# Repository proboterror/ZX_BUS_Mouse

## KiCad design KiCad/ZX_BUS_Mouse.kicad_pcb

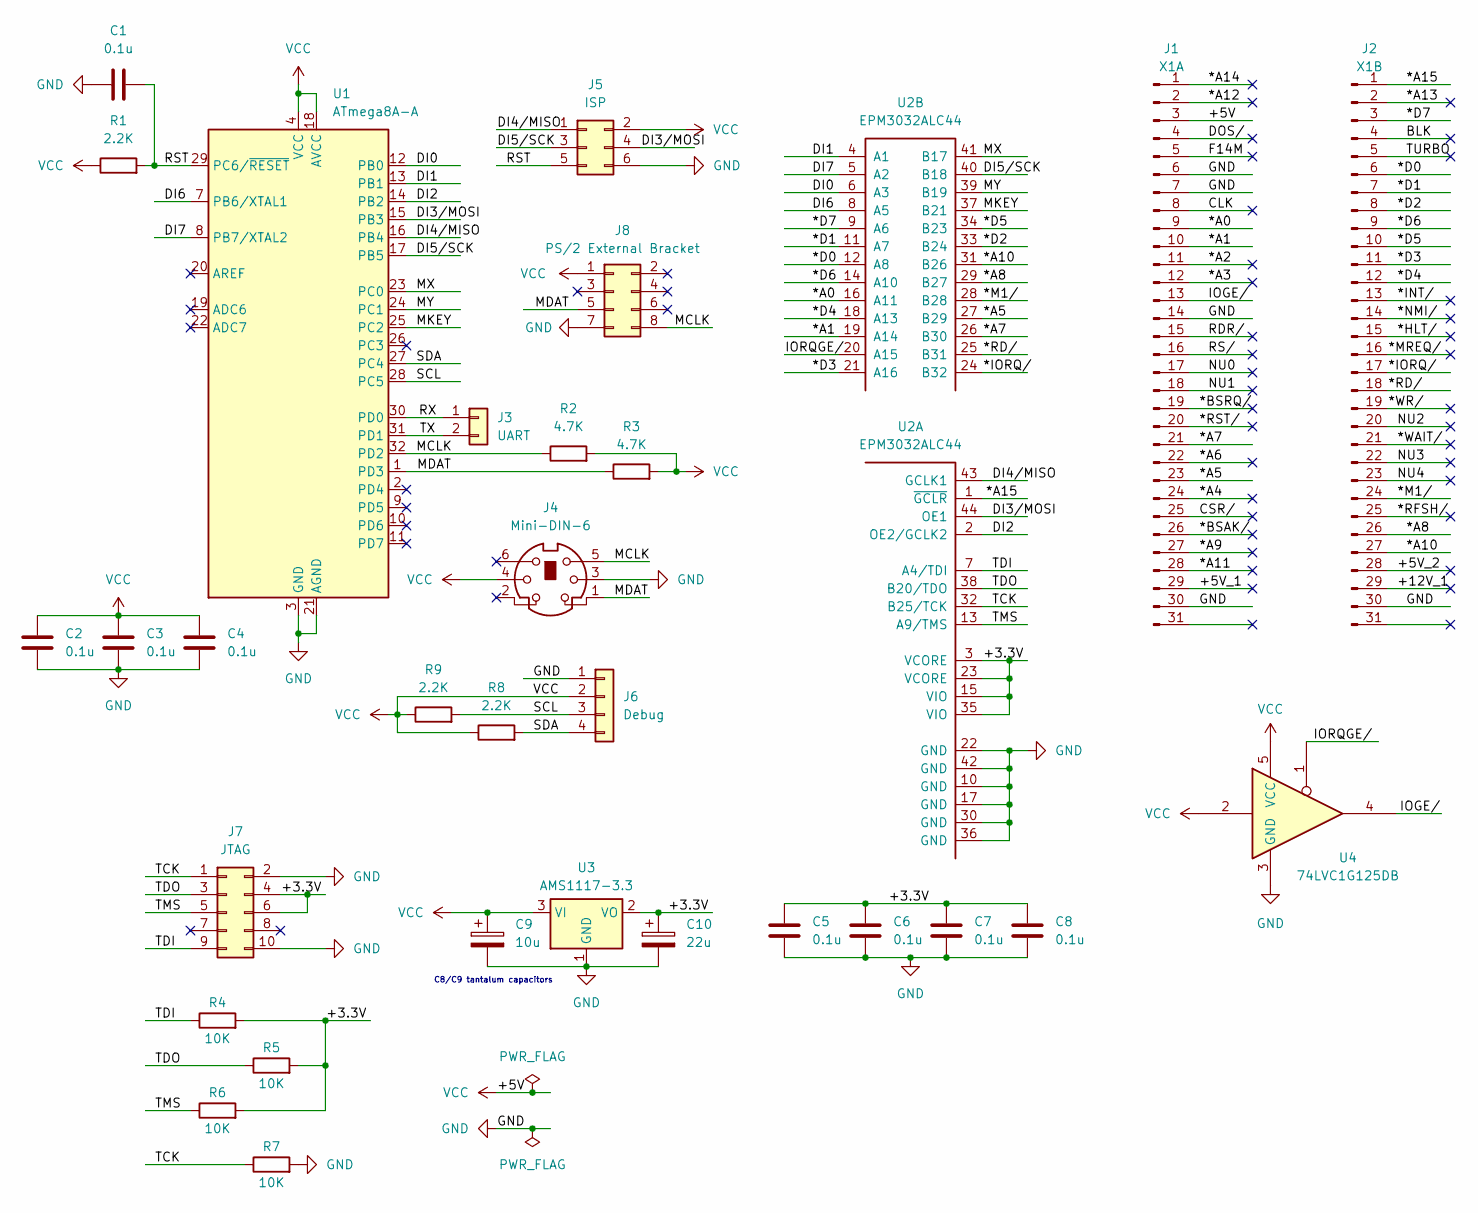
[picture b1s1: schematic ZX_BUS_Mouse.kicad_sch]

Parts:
C1, C2, C3, C4, C5, C6, C7, C8: 0.1u; C_1206_3216Metric_Pad1.33x1.80mm_HandSolder
C9: 10u; CP_EIA-6032-28_Kemet-C_Pad2.25x2.35mm_HandSolder
C10: 22u; CP_EIA-6032-28_Kemet-C_Pad2.25x2.35mm_HandSolder
J1: X1A; PinSocket_1x31_P2.54mm_2
J2: X1B; PinSocket_1x31_P2.54mm_2
J3: UART; PinHeader_1x02_P2.54mm_Vertical
J4: Mini-DIN-6; Connector_Mini-DIN_Female_6Pin_2rows
J5: ISP; PinHeader_2x03_P2.54mm_Vertical
J6: Debug; PinHeader_1x04_P2.54mm_Vertical
J7: JTAG; IDC-Header_2x05_P2.54mm_Vertical
J8: PS/2 External Bracket; PinHeader_2x04_P2.54mm_Vertical
R1, R8, R9: 2.2K; R_1206_3216Metric_Pad1.30x1.75mm_HandSolder
R2, R3: 4.7K; R_1206_3216Metric_Pad1.30x1.75mm_HandSolder
R4, R5, R6, R7: 10K; R_1206_3216Metric_Pad1.30x1.75mm_HandSolder
U1: ATmega8A-A; TQFP-32_7x7mm_P0.8mm
U2: EPM3032ALC44; PLCC-44_THT-Socket; MPN EPM3032ALC44-{grade}
U3: AMS1117-3.3; SOT-223-3_TabPin2
U4: 74LVC1G125DB; SOT-23-5_HandSoldering

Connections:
/*A0: J1.9, U2.16 (A11)
/*A1: J1.10, U2.19 (A14)
/*A2: J1.11
/*A3: J1.12
/*A4: J1.24
/*A5: J1.23, U2.27 (B29)
/*A6: J1.22
/*A7: J1.21, U2.26 (B30)
/*A8: J2.26, U2.29 (B27)
/*A9: J1.27
/*A10: J2.27, U2.31 (B26)
/*A11: J1.28
/*A12: J1.2
/*A13: J2.2
/*A14: J1.1
/*A15: J2.1, U2.1 (~GCLR)
/*BSAK/: J1.26
/*BSRQ/: J1.19
/*D0: J2.6, U2.12 (A8)
/*D1: J2.7, U2.11 (A7)
/*D2: J2.8, U2.33 (B24)
/*D3: J2.11, U2.21 (A16)
/*D4: J2.12, U2.18 (A13)
/*D5: J2.10, U2.34 (B23)
/*D6: J2.9, U2.14 (A10)
/*D7: J2.3, U2.9 (A6)
/*HLT/: J2.15
/*INT/: J2.13
/*IORQ/: J2.17, U2.24 (B32)
/*M1/: J2.24, U2.28 (B28)
/*MREQ/: J2.16
/*NMI/: J2.14
/*RD/: J2.18, U2.25 (B31)
/*RFSH/: J2.25
/*RST/: J1.20
/*WAIT/: J2.21
/*WR/: J2.19
/+3.3V: C5.1, C6.1, C7.1, C8.1, C10.1, J7.4, J7.6, R4.2, R5.2, R6.2, U2.3 (VCORE), U2.15 (VIO), U2.23 (VCORE), U2.35 (VIO), U3.2 (VO)
/+5V_1: J1.29
/+5V_2: J2.28
/+12V_1: J2.29
/BLK: J2.4
/CLK: J1.8
/CSR/: J1.25
/DI0: U1.12 (PB0), U2.6 (A3)
/DI1: U1.13 (PB1), U2.4 (A1)
/DI2: U1.14 (PB2), U2.2 (OE2/GCLK2)
/DI3/MOSI: J5.4, U1.15 (PB3), U2.44 (OE1)
/DI4/MISO: J5.1, U1.16 (PB4), U2.43 (GCLK1)
/DI5/SCK: J5.3, U1.17 (PB5), U2.40 (B18)
/DI6: U1.7 (PB6/XTAL1), U2.8 (A5)
/DI7: U1.8 (PB7/XTAL2), U2.5 (A2)
/DOS/: J1.4
/F14M: J1.5
/IOGE/: J1.13, U4.4
/IORQGE/: U2.20 (A15), U4.1
/MCLK: J4.5, J8.8, R2.1, U1.32 (PD2)
/MDAT: J4.1, J8.5, R3.1, U1.1 (PD3)
/MKEY: U1.25 (PC2), U2.37 (B21)
/MX: U1.23 (PC0), U2.41 (B17)
/MY: U1.24 (PC1), U2.39 (B19)
/NU0: J1.17
/NU1: J1.18
/NU2: J2.20
/NU3: J2.22
/NU4: J2.23
/RDR/: J1.15
/RST: C1.2, J5.5, R1.2, U1.29 (PC6/~RESET)
/RS/: J1.16
/RX: J3.1, U1.30 (PD0)
/SCL: J6.3, R9.2, U1.28 (PC5)
/SDA: J6.4, R8.2, U1.27 (PC4)
/TCK: J7.1, R7.1, U2.32 (B25/TCK)
/TDI: J7.9, R4.1, U2.7 (A4/TDI)
/TDO: J7.3, R5.1, U2.38 (B20/TDO)
/TMS: J7.5, R6.1, U2.13 (A9/TMS)
/TURBO: J2.5
/TX: J3.2, U1.31 (PD1)
GND: C1.1, C2.2, C3.2, C4.2, C5.2, C6.2, C7.2, C8.2, C9.2, C10.2, J1.6, J1.7, J1.14, J1.30, J2.30, J4.3, J5.6, J6.1, J7.2, J7.10, J8.7, R7.2, U1.3 (GND), U1.5 (GND), U1.21 (AGND), U2.10 (GND), U2.17 (GND), U2.22 (GND), U2.30 (GND), U2.36 (GND), U2.42 (GND), U3.1 (GND), U4.3 (GND)
VCC: C2.1, C3.1, C4.1, C9.1, J1.3, J4.4, J5.2, J6.2, J8.1, R1.1, R2.2, R3.2, R8.1, R9.1, U1.4 (VCC), U1.6 (VCC), U1.18 (AVCC), U3.3 (VI), U4.2, U4.5 (VCC)

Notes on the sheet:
C8/C9 tantalum capacitors

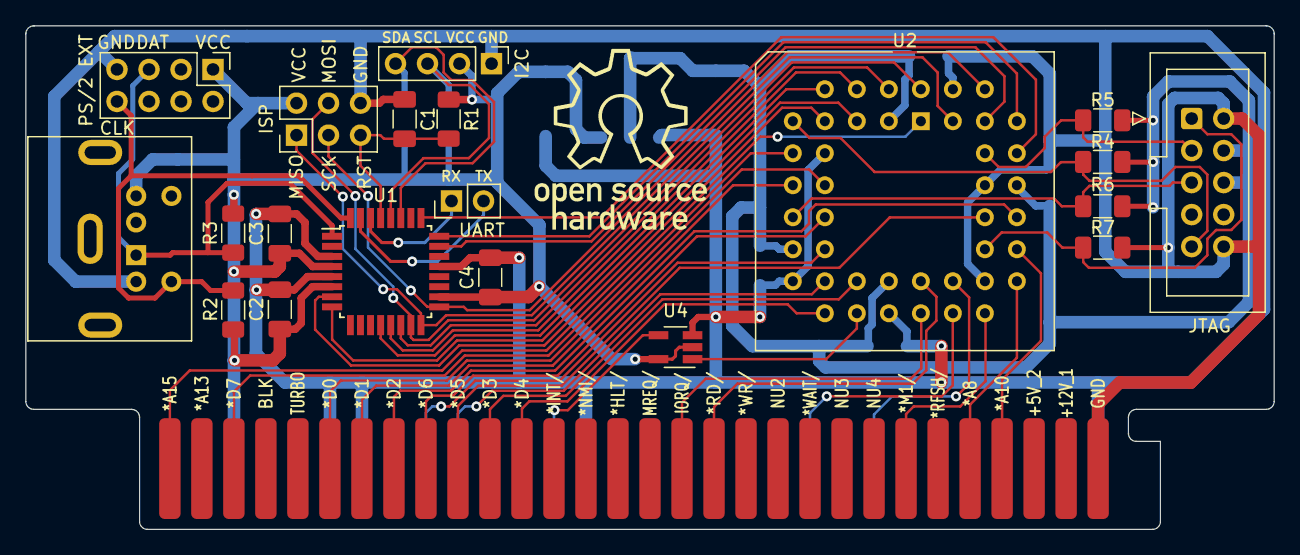
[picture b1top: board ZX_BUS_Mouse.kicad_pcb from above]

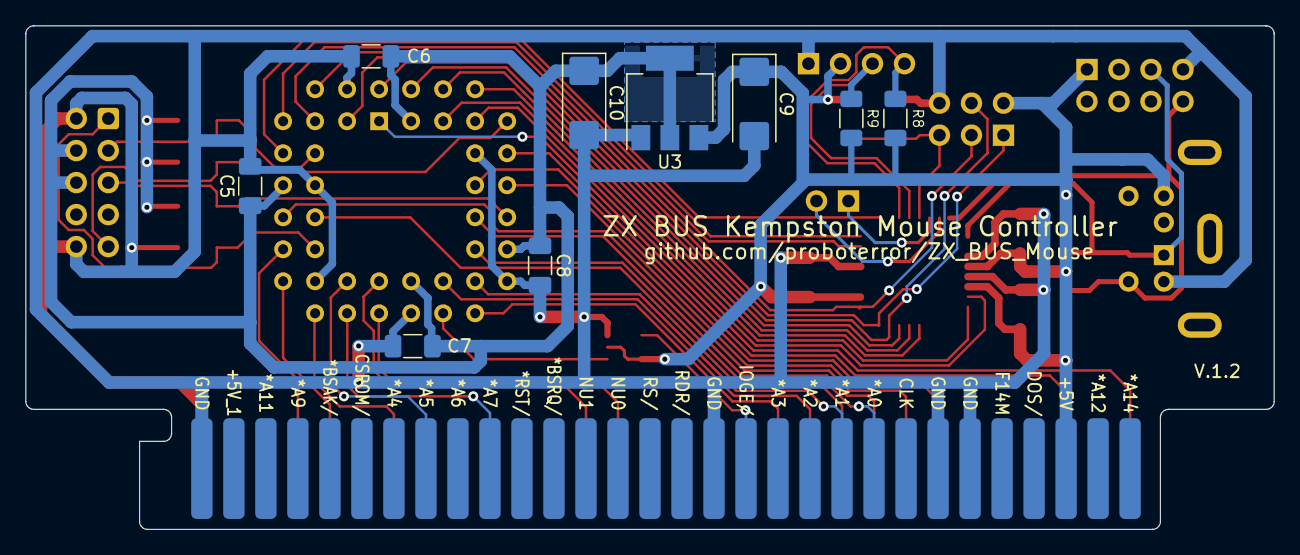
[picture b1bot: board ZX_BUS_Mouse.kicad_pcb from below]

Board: 2 copper layers, 99.1 x 40.0 mm, 31 parts (10 on the bottom side), 45 nets.

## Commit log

2024-04-19 ZX Bus Mouse controller inital schematic. Schematic borrowed from Deltagon 1.5 (C) @djking26, Игорь Матвеев @azx987sa. ZX Bus prototype PCB from https://github.com/AlexEkb4ever/ZX_BUS Altera MAX 3000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
    Changes from:
    Added ATmega ISP connector, debug screen I2C connector.
    Decoupling capacitors for each ATmega / Altera power line.
    Optional capacitor on ATmera RESET.
    Tantalum capacitors for AM51117 input / output.
    OIRQ input split to IORQ input / IOGE output.
2024-04-19 Add debug I2C connector on PCB. Disable solder mask on edge connector.
2024-04-19 Board height 40 mm.
2024-04-19 Correct SDA pullup resistor.
2024-04-19 Connect I2C to VCC and GND.
2024-04-19 Route PCB. Reassign EPM3032 IO pins.
2024-04-19 Add labels to PCB.
2024-04-19 Add reference url: https://github.com/4x1md/kicad_libraries/blob/master/Custom_Footprints.pretty/Connector_Mini-DIN_Female_6Pin_2rows.kicad_mod
2024-04-19 Arrange resistors references.
2024-04-19 Add logo to PCB.
2024-04-19 Rename libs/my_lib.pretty libs/zx_bus.pretty.
2024-04-19 Align PCB F.Fab labels.
2024-04-19 Remove unused 2x30 connector from PCB.
2024-04-19 Rename my_lib library to zx_bus. Move Connector_Mini-DIN_Female_6Pin.pretty to libs/.
2024-04-19 Move to KiCad/ folder.
2024-04-19 Test production gerbers.
2024-04-19 Move to gerber/ folder.
2024-04-19 Initial PS/2 mouse support with mouse wheel. Implementation without PS/2 clock signal change interrupt usage. https://github.com/Sylaina/oled-display used for debug OLED screen output. Makefile to be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
2024-04-19 Add ZX Bus interface registers data output. Fix compiler warnings.
2024-04-19 Add code references.
2024-04-19 Fixed PS/2 mouse init after power on. Invert mouse buttons state values. Check and match mouse wheel / buttons / axis behaviour with available specs and Unreal Speccy 0.39.0. Set initial Kempston mou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
    Add Kempston mouse wheel support references.
    Move ENABLE_WHEEL define to Makefile.
    Change mouse axis data to uint8_t.
    Replace delays magic numbers with named defines.
    Replace defines with typed enum mouse_pin_t.
    Add debug messages for PS/2 i
2024-04-19 .clang-format added.
2024-04-19 Arrange defines.
2024-04-19 Move to source/ATmega/ folder.
2024-04-19 Mouse controller initial VHDL implementation. No mouse wheel support. 31 of 32 macrocells, 33 of 34 IO pins used. Deltagon IO pins assinments.
2024-04-19 Optimize out entity address_decoder.
2024-04-19 Pin assignment matching PCB.
2024-04-19 Add example for enable mouse wheel. Cleanup outdated comments.
2024-04-19 Fixed #FADF mouse buttons port. Assume output is always 8-bit wide. Unused data bits in output should be set to 1.
2024-04-19 Move to source/Altera-VHDL/ folder.
2024-04-20 Update PCB dimensions drawings.
2024-04-20 Add reference Deltagon 1.5 mouse controller schematic.
2024-04-20 Disable ATmega debug code.
2024-04-20 Add MousTest (C) 2012 Patrik Rak - Raxoft
2024-04-20 Add documentation images.
2024-04-20 Add OSHW logo source.
2024-04-20 Add compiled ATmega firmware.
2024-04-20 Add board photos.
2024-04-21 Add ZX Evolution source reference.
2024-04-21 Add README.MD.
2024-04-21 Update README.MD.
2024-04-22 Set MKEY register mouse wheel bits to 1111 if mouse wheel not presented.
2024-09-20 Fix PCB backface ZX-BUS pins silkscreen labels.
2024-09-20 Update PCB images.
2024-09-20 Update gerbers.
2024-11-26 Fix schematic ERC warnings.
2024-11-26 Add 74LVC1G125DB 3-state buffer for IORQGE/IOGE signal: 5V output signal level. Resolve issue with ZX-BUS XTRaiser, prevent potential issues with 5V IORQGE back current from other cards to CPLD outpu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
2024-11-26 Add external PS/2 mouse bracket connector (common 486-Pentium AT motherboards pinout). Add debug UART connector (RX/TX). Move I2C debug connector, move optional R8, R9 pullup resistors to backside. C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
2024-11-26 Extend ZX-BUS edge connector width from 80 to 81 mm (+0.5 mm from right and left).
    Reference:
    IBM 5150 Technical Reference manual, page 54
    http://www.minuszerodegrees.net/manuals/IBM_5150_Technical_Reference_6322507_APR84.pdf
2024-11-26 Update description, add versions info and ToDo.
2024-11-27 Replace CPLD VHDL implementation with simplified Verilog one. Optimize to 32 macrocells used with 3rd mouse button disabled.
2024-11-29 Test ATmega source implementation using Arduino PS2Mouse library from http://github.com/kristopher/PS2-Mouse-Arduino/ Mouse wheel not supported.
2024-11-29 Add compiled ATmega8 Arduino firmware.
2025-01-25 Add .gitignore.
2025-01-29 Expand Scorpion IBM keyboard and mouse controller description.
2025-01-29 Add PS/2 interface debug ATmega firmware and description.
2025-02-10 Move CPLD registers startup values init before PS/2 mouse init. Reduce CPLD register set strobe from 10 us to 1 us.
2025-02-11 Set initial Kempston mouse controller register values: MX: 0x80, MY: 0x60, MKEY: 0xFF (Mr Gluk Reset Service 6.63 expects bits 0-2 (3 buttons) set to 1 for mouse detect).
2025-03-11 Quirk to fit in EPM3032 32 macrocells limitation with mouse wheel and 3 buttons support. Assume only one button can be pressed and sent to MKEY controller register at a time. Requires matching MCU an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
2025-03-18 Extended PS/2 bidirectional synchronous serial protocol comments.
2025-03-19 New MCU code implementation using hardware PS/2 clock signal change interrupt.
    Based on avr-mouse-ps2-to-serial firmware source by Oleg Trifonov https://github.com/trol73/avr-mouse-ps2-to-serial
2025-03-19 Update compiled firmware.
2025-03-19 PS/2 host inhibit: - Remove unnecessary pull clock/data up before pulling clock down. - Reduce inhibit clock signal length to 100 us according to specification.
2025-03-19 Update compiled ATmega firmware.
2025-03-19 Makefile: set actual ATmega8 fuses values for AVRDude.
2025-03-25 uint8_t ps2_rx_buf_count cannot exceed 255.
2025-03-25 Async PS/2 mouse interface implementation with init within main update loop. mouse_init_protocol sequence converted to state machine. Use timer poll instead of watchdog reboot to restart init loop on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
2025-04-05 V.1.1. Add PCB version label. Update README.MD.
2025-06-03 Scorpion ZS 256 Service ROM / ProfROM by @LW_aka_PLM: fixed ROM Disk loading with mouse enabled. Added A15 to IORQGE / ports addresses decode.
2025-07-05 Add build prerequisites info.
2025-11-24 V.1.2 gerbers.
